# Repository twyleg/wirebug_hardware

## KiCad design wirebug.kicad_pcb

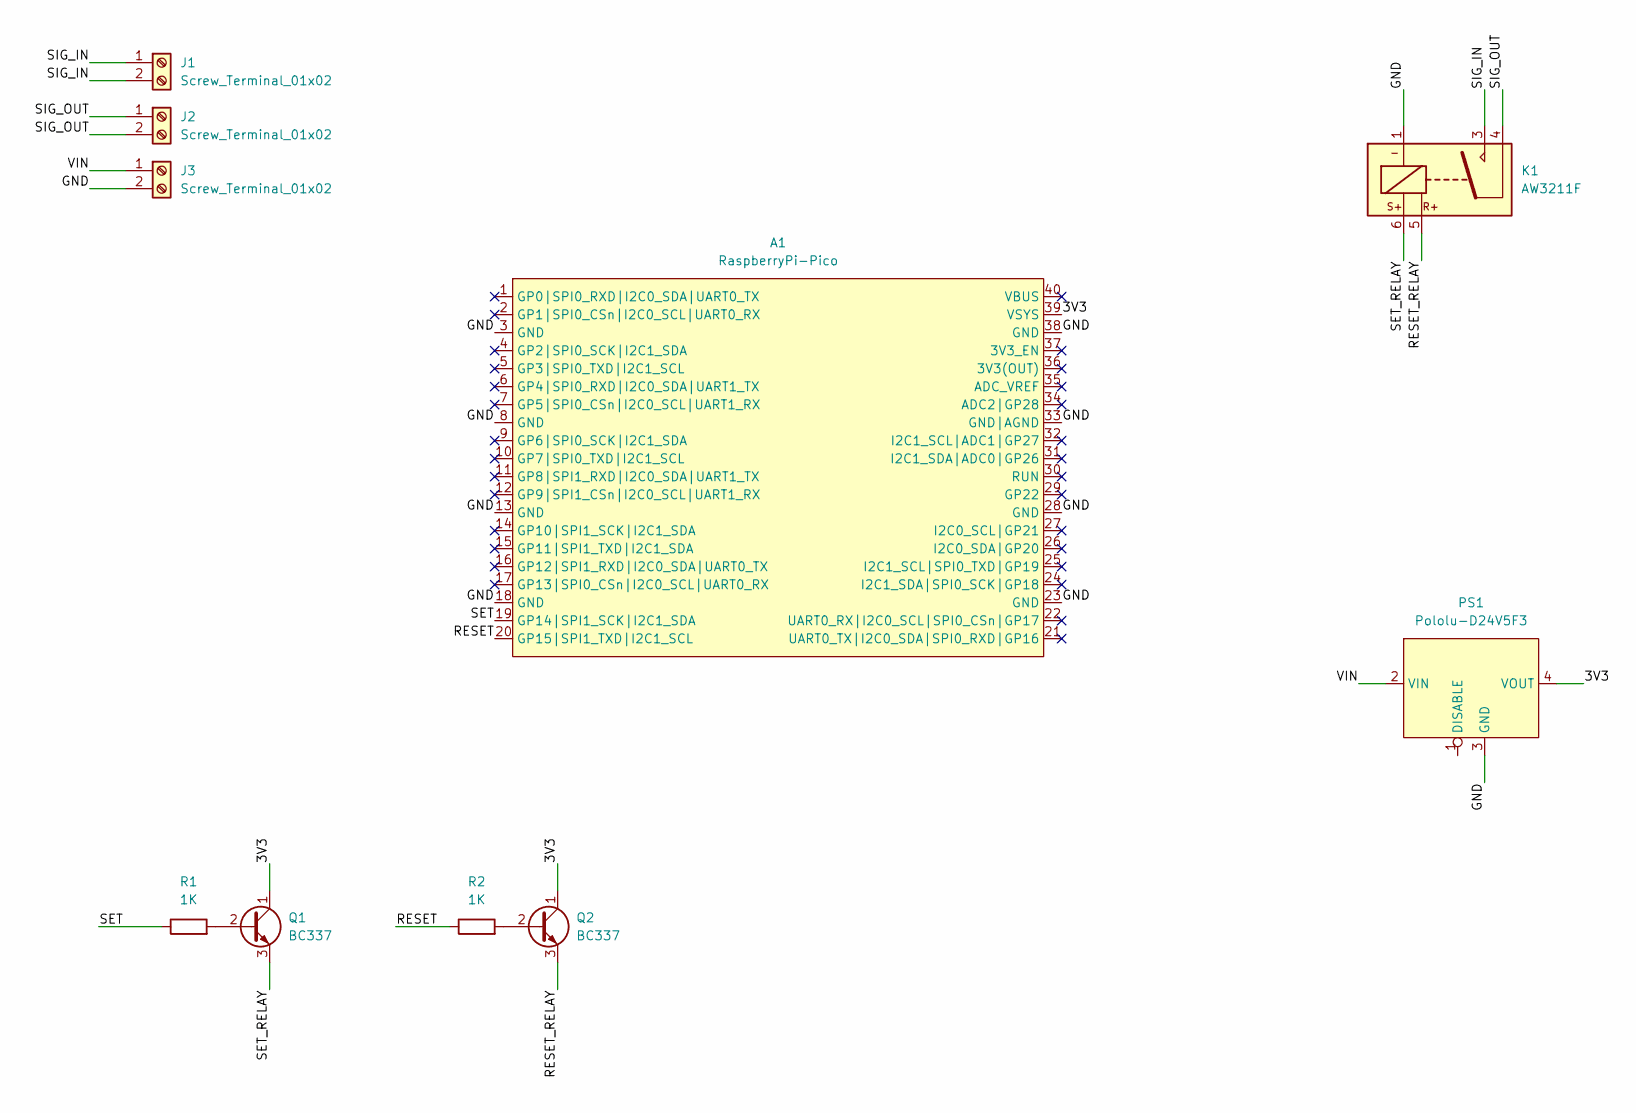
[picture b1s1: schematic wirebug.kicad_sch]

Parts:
A1: RaspberryPi-Pico; RaspberryPiPico-THT-Dev
J1, J2, J3: Screw_Terminal_01x02; TerminalBlock_MetzConnect_Type101_RT01602HBWC_1x02_P5.08mm_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
K1: AW3211F; Relay_Panasonic_AW3211F_THT
PS1: Pololu-D24V5F3; Pololu-D24V5F3-Dev
Q1, Q2: BC337; TO-92_Inline
R1, R2: 1K; R_Axial_DIN0207_L6.3mm_D2.5mm_P2.54mm_Vertical

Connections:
/3V3: A1.39 (VSYS), PS1.4 (VOUT), Q1.1 (C), Q2.1 (C)
/GND: A1.3 (GND), A1.8 (GND), A1.13 (GND), A1.18 (GND), A1.23 (GND), A1.28 (GND), A1.33 (GND|AGND), A1.38 (GND), J3.2, K1.1, PS1.3 (GND)
/RESET: A1.20 (GP15|SPI1_TXD|I2C1_SCL), R2.1
/RESET_RELAY: K1.5, Q2.3 (E)
/SET: A1.19 (GP14|SPI1_SCK|I2C1_SDA), R1.1
/SET_RELAY: K1.6, Q1.3 (E)
/SIG_IN: J1.1, J1.2, K1.3
/SIG_OUT: J2.1, J2.2, K1.4
/VIN: J3.1, PS1.2 (VIN)
unnamed: Q1.2 (B), R1.2
unnamed: Q2.2 (B), R2.2

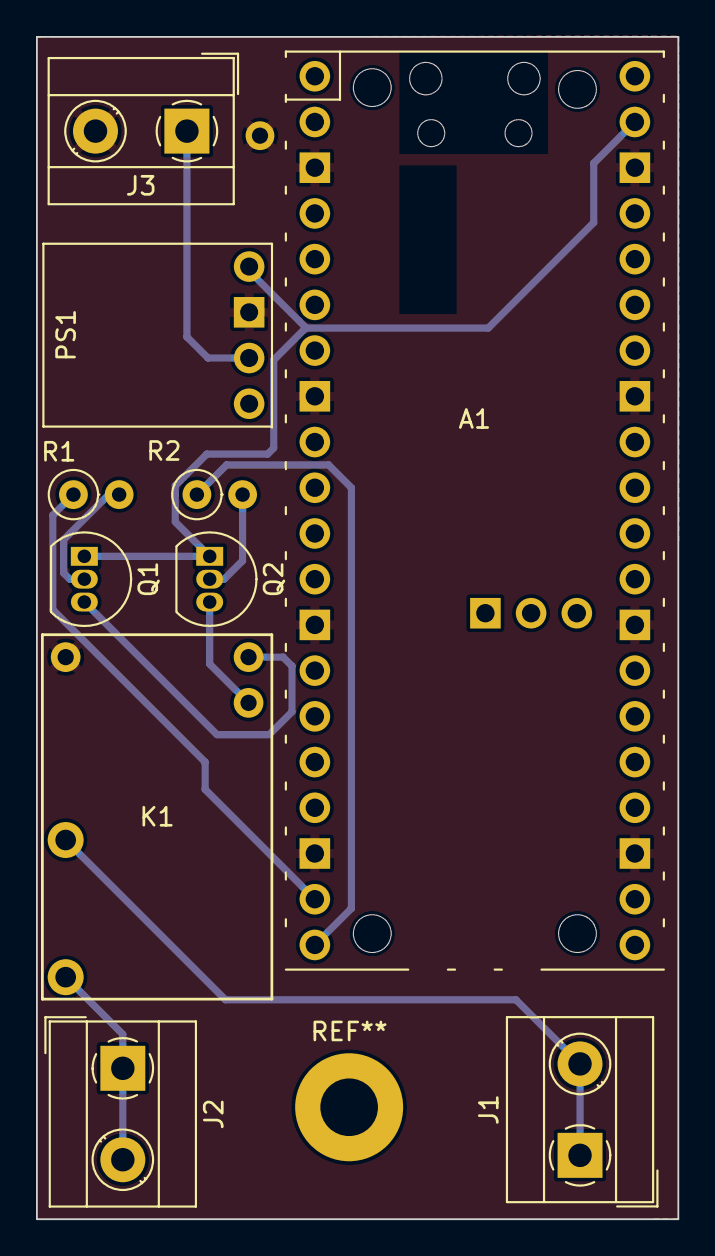
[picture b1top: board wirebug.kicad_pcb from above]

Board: 2 copper layers, 35.6 x 65.7 mm, 10 parts (0 on the bottom side), 11 nets.

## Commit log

2023-12-02 Init project
2023-12-02 First draft
2023-12-02 Fixed github action
2023-12-02 Generated exports
2023-12-02 Updated footprint to resolve missing 3d model
2023-12-02 Trying to fix missing object in 3d rendering
2023-12-20 Added requirements.txt
2023-12-20 Cleaned up kibot config and moved it from kicad utils back to project
2023-12-22 Updated structure
2023-12-22 Generated docs
2024-01-07 Updated PicoW and voltage regultator
2024-01-08 Smaller changes
